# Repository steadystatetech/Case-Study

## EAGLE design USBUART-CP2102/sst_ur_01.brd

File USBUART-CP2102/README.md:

USB to UART CP2102 based board :
==========

STEADYSTATE TECHNOLOGIES developed a USB to UART board. These are the files which we used to generate the GERBER files. Here we used Eagle cad for developing the prototype.

Files:
==========
sst_ur_01.sch 	- Schematics file
sst_ur_01.brd 	- PCB board file
logo.brd	- PCB board file of our logo.

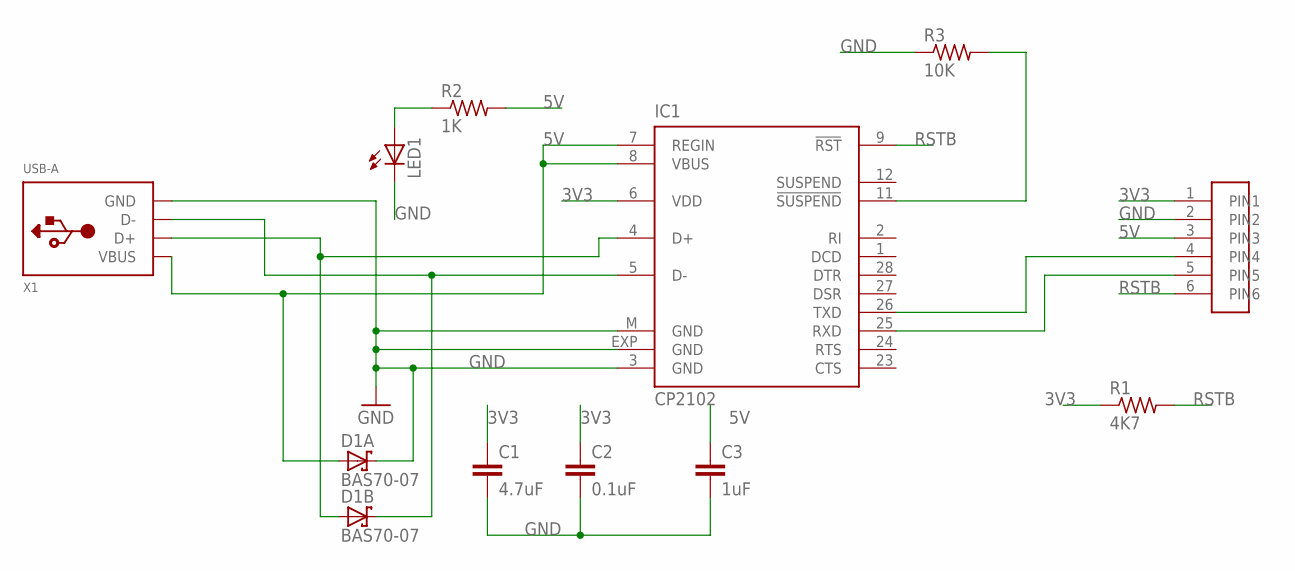
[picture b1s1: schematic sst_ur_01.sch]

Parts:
C1: 4.7uF; C3216
C2: 0.1uF; C1206
C3: 1uF; C1206
D1: BAS70-07; SOT143-R
IC1: CP2102; MLP28
LED1: LEDCHIPLED_1206; CHIPLED_1206
R1: 4K7; R1210
R2: 1K; R1210
R3: 10K; R1210
U$1: SIL6
X1: USB-A; MOLEX_480371000

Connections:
3V3: C1.1, C2.1, IC1.6 (VDD), R1.1, U$1.1 (PIN1)
5V: C3.1, D1.4 (A), IC1.7 (REGIN), IC1.8 (VBUS), R2.2, U$1.3 (PIN3), X1.1 (VBUS)
GND: C1.2, C2.2, C3.2, D1.1 (C), IC1.3 (GND), IC1.EXP (GND), IC1.M (GND), LED1.C, R3.1, U$1.2 (PIN2), X1.4 (GND)
unnamed: D1.2 (C), IC1.5 (D-), X1.2 (D-)
unnamed: IC1.11 (!SUSPEND), R3.2
unnamed: D1.3 (A), IC1.4 (D+), X1.3 (D+)
unnamed: LED1.A, R2.1
unnamed: IC1.26 (TXD), U$1.4 (PIN4)
unnamed: IC1.25 (RXD), U$1.5 (PIN5)
RSTB: IC1.9 (!RST), R1.2, U$1.6 (PIN6)

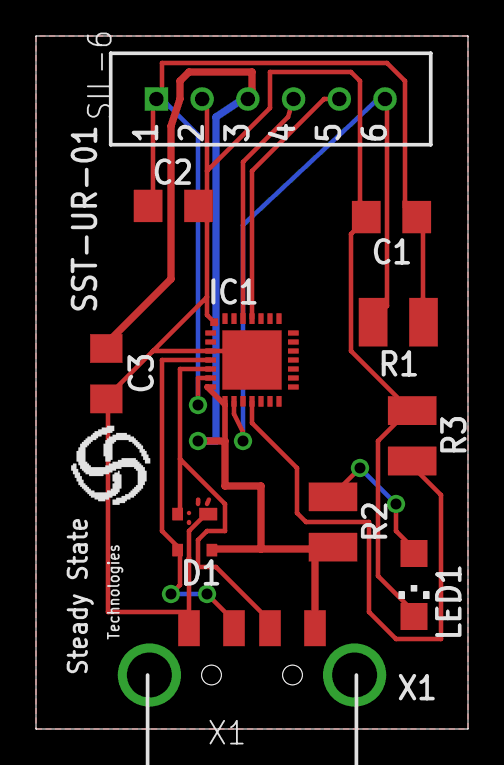
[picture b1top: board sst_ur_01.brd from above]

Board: 2 copper layers, 24.0 x 38.5 mm, 11 parts (0 on the bottom side), 10 nets.

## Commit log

2014-07-10 Added the schematics and pcb files of USBUART project.
2014-07-10 Changed the description
